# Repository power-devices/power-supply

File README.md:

# Welcome to the Power Supply electronics repository

I teach power electronics and I want to provide my students the best experience possible. This is the reason I created this project. I intend to allow people to produce power electronics devices at an extreme low cost. This board required only 2 layers, but this is no problem today due to [JLCPCB](https://jlcpcb.com/) or other manufacturers.

So far, the project is divided into 3 pieces:

 1. Power supply: used to delivery power the other boards, it is compatible with mono-three phase up to 220 VAC
 2. Power bullet: a three phase h-bridge, simple as that
 3. Power brain F103: the main controller

# Disclaimer

I provide no warranty at all. Use it at your own risk!

# What will I find here?

You will find the design and production files. To edit the schematic/board you will need to install Kicad. I used version 7 to create this board.

# What can I do with this?

In this repository the board design and production files are stored. You are welcome to download/distribute it, use it, whatever.

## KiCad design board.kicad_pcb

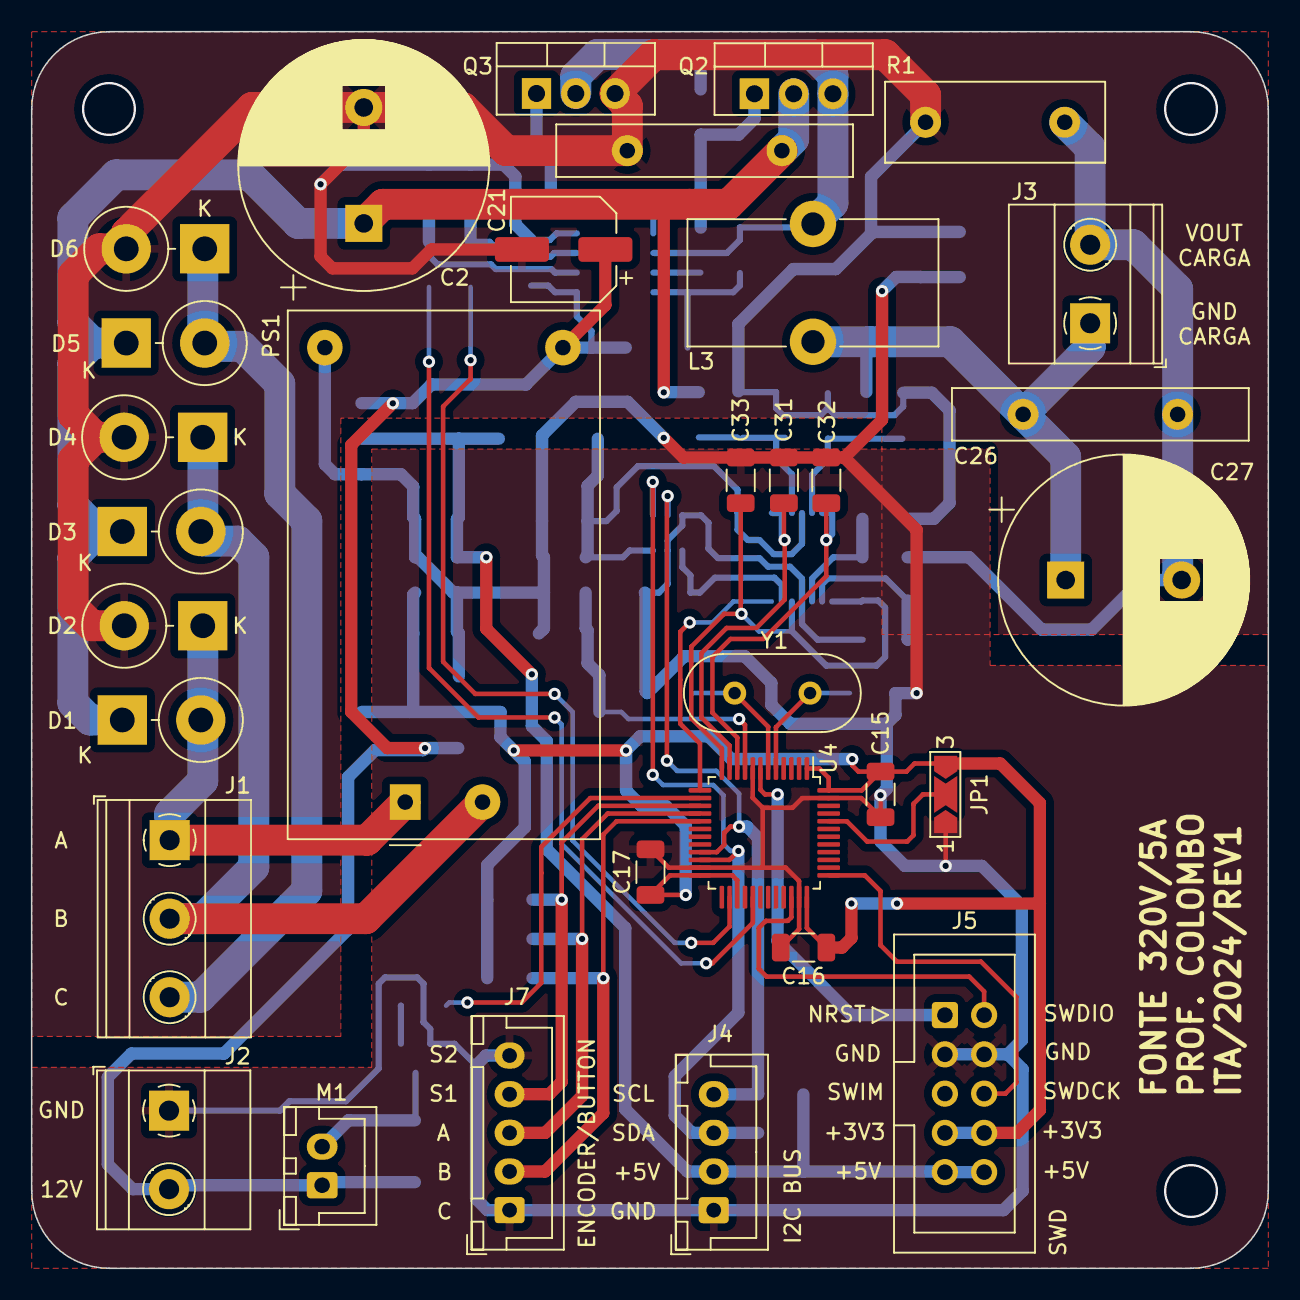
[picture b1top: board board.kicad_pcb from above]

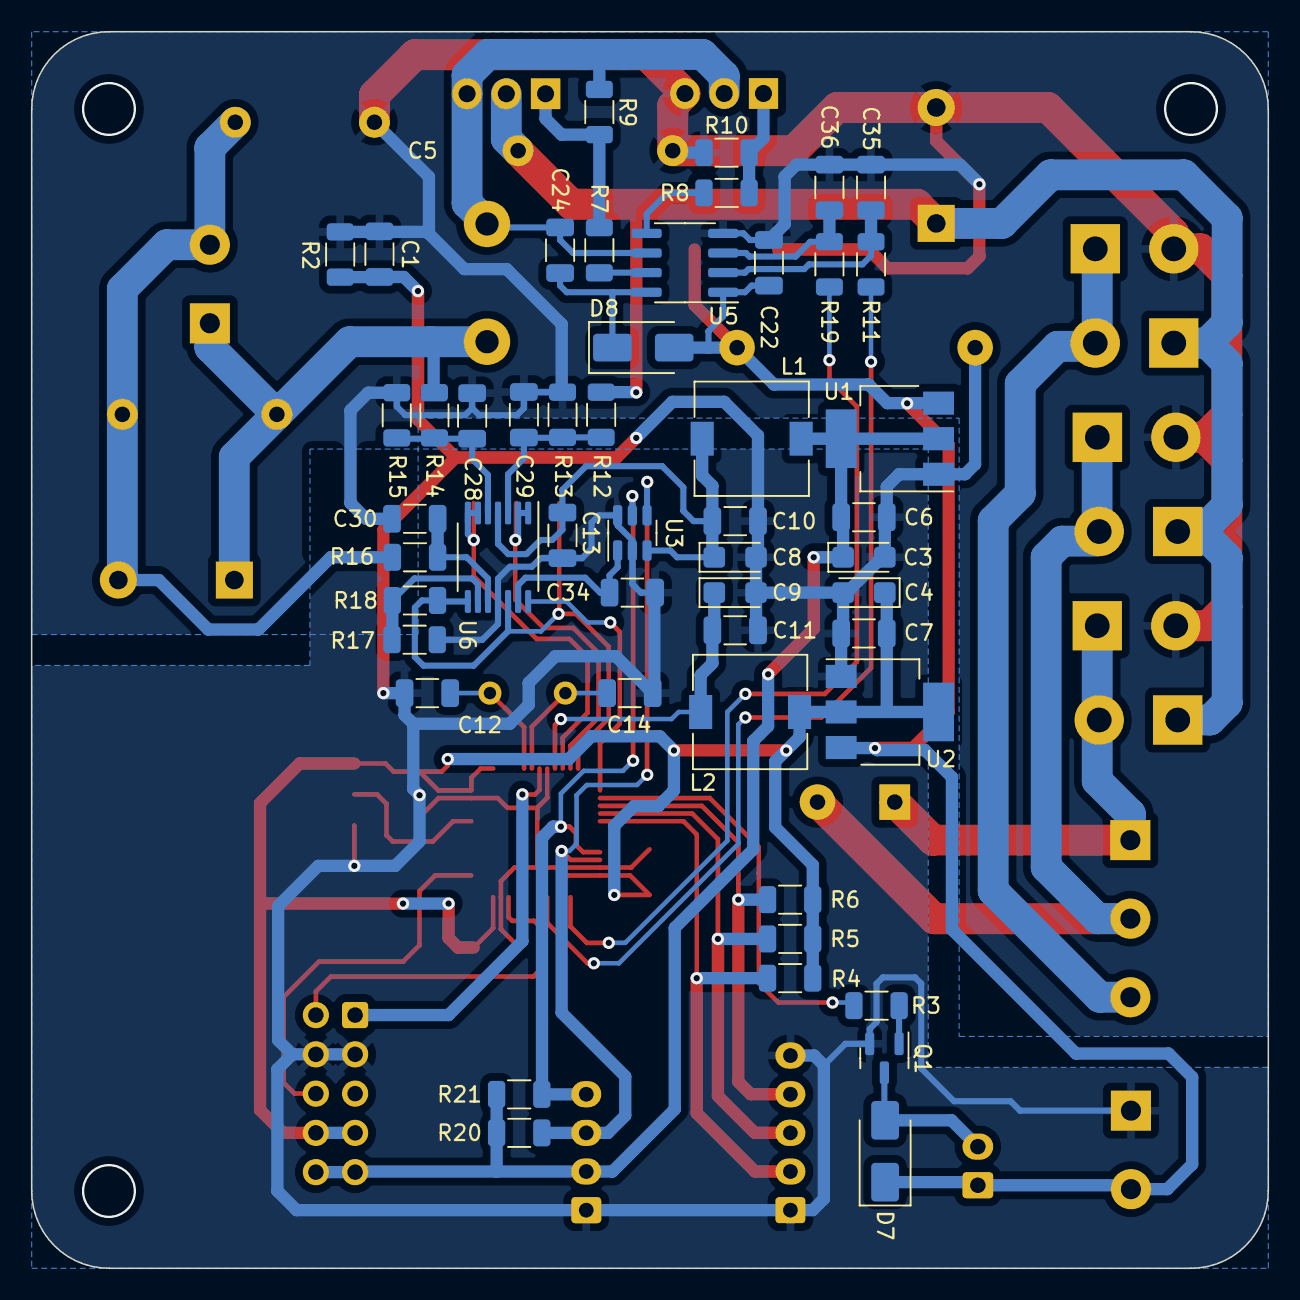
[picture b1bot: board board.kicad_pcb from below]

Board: 2 copper layers, 80.0 x 80.0 mm, 82 parts (50 on the bottom side), 46 nets.

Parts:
C1, C6, C7, C10, C11, C15, C22, C24: 1uF; C_1206_3216Metric
C2, C27: 47uF; CP_Radial_D16.0mm_P7.50mm
C3, C4, C8, C9: 10uF; CP_EIA-3216-18_Kemet-A
C5, C26: 100nF; C_Disc_D19.0mm_W3.0mm_P10.00mm
C12, C14: 22pF; C_1206_3216Metric
C13, C16, C17: 100nF; C_1206_3216Metric
C21: 100uF; CP_Elec_6.3x7.7
C28, C29: 2n2; C_1206_3216Metric
C30: 3n3; C_1206_3216Metric
C31, C32, C33, C34: 10nF; C_1206_3216Metric
C35, C36: 33nF; C_1206_3216Metric
D1, D2, D3, D4, D5, D6: 1N5408; D_DO-201AD_P5.08mm_Vertical_KathodeUp
D7: SS14; D_SMA
D8: 1N4007; D_SMA
J1: Screw_Terminal_01x03; TerminalBlock_Phoenix_MKDS-1,5-3-5.08_1x03_P5.08mm_Horizont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
J2, J3: Screw_Terminal_01x02; TerminalBlock_Phoenix_MKDS-1,5-2-5.08_1x02_P5.08mm_Horizont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
J4: I2C; JST_XH_B4B-XH-A_1x04_P2.50mm_Vertical
J5: SWD; IDC-Header_2x05_P2.54mm_Vertical
J7: ENCODER; JST_XH_B5B-XH-A_1x05_P2.50mm_Vertical
JP1: SolderJumper-3_P2.0mm_Open_TrianglePad1.0x1.5mm_NumberLabels
L1, L2: 100uH; L_7.3x7.3_H4.5
L3: 1mH; L_Toroid_Vertical_L16.0mm_W8.0mm_P7.62mm
M1: Fan; JST_XH_B2B-XH-A_1x02_P2.50mm_Vertical
PS1: HLK-PM12; Converter_ACDC_HiLink_HLK-PMxx
Q1: MMBT3904; SOT-23
Q2, Q3: FDP11N50; TO-220-3_Vertical
R1: 0R1; R_Box_L14.0mm_W5.0mm_P9.00mm
R2: 1R; R_1206_3216Metric
R3, R16: 1k; R_1206_3216Metric
R4, R5, R6, R20, R21: 3k3; R_1206_3216Metric
R7, R8: 47R; R_1206_3216Metric
R9, R10: 10k; R_1206_3216Metric
R11, R19: 100R; R_1206_3216Metric
R12, R14: 180k; R_1206_3216Metric
R13, R15: 1k5; R_1206_3216Metric
R17: 6k8; R_1206_3216Metric
R18: 33k; R_1206_3216Metric
U1: AMS1117-5.0; SOT-223-3_TabPin2
U2: AMS1117-3.3; SOT-223-3_TabPin2
U3: MCP4725xxx-xCH; SOT-23-6
U4: STM32F103C8Tx; LQFP-48_7x7mm_P0.5mm
U5: IR2101; SOIC-8_3.9x4.9mm_P1.27mm
U6: LM324; TSSOP-14_4.4x5mm_P0.65mm
Y1: 16MHz; Crystal_HC49-4H_Vertical

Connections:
+3.3V: C4.1, C7.1, C15.1, C16.1, C17.1, J5.7, J5.8, JP1.3 (B), L2.1, R4.1, R5.1, R6.1, U2.2 (VO), U4.1 (VBAT), U4.24 (VDD), U4.27 (PB14), U4.36 (VDD), U4.48 (VDD)
+3.3VA: C9.1, C11.1, L2.2, U4.9 (VDDA)
+5V: C3.1, C6.1, J4.2, J5.9, J5.10, L1.1, R20.1, R21.1, U1.2 (VO)
+5VA: C8.1, C10.1, C13.1, L1.2, U3.3 (VDD), U6.4 (V+)
+12V: C21.1, C22.1, D7.1 (K), D8.2 (A), J2.2, M1.1 (+), PS1.4 (+Vout), U1.3 (VI), U2.3 (VI), U5.1 (VCC)
/AC-CC converter/PHASE_A: D1.2 (A), D2.1 (K), J1.1, PS1.1 (AC/L)
/AC-CC converter/PHASE_B: D3.2 (A), D4.1 (K), J1.2, PS1.2 (AC/N)
/AC-CC converter/PHASE_C: D5.2 (A), D6.1 (K), J1.3
/Driver/GND_OUT: C26.2, C27.2, J3.2, R1.1, R16.1
/Driver/HIN: R11.1, U4.29 (PA8)
/Driver/LIN: R19.1, U4.26 (PB13)
/Driver/VOUT: C26.1, C27.1, J3.1, L3.1, R14.1
/MCU/BOOT0: JP1.2 (C), U4.44 (BOOT0)
/MCU/BUTTON: J7.4, R6.2, U4.15 (PA5)
/MCU/ENCODER_A: J7.3, R5.2, U4.16 (PA6)
/MCU/ENCODER_B: J7.2, R4.2, U4.17 (PA7)
/MCU/FAN: R3.1, U4.14 (PA4)
/MCU/IMAX: C34.1, U3.1 (VOUT), U6.13 (-)
/MCU/NRST: J5.1, U4.7 (NRST)
/MCU/OC: U4.13 (PA3), U6.14
/MCU/SCL: J4.4, R21.2, U3.5 (SCL), U4.21 (PB10)
/MCU/SDA: J4.3, R20.2, U3.4 (SDA), U4.22 (PB11)
/MCU/SENSE_IOUT: C33.1, R18.2, U4.12 (PA2), U6.8, U6.12 (+)
/MCU/SENSE_VIN: C31.1, U4.11 (PA1), U6.1, U6.2 (-)
/MCU/SENSE_VOUT: C32.1, U4.10 (PA0), U6.6 (-), U6.7
/MCU/SWDCK: J5.6, U4.37 (PA14)
/MCU/SWDIO: J5.2, U4.34 (PA13)
/MCU/XTAL1: C12.1, U4.5 (PD0), Y1.1
/MCU/XTAL2: C14.1, U4.6 (PD1), Y1.2
GNDA: C1.1, C3.2, C4.2, C6.2, C7.2, C8.2, C9.2, C10.2, C11.2, C12.2, C13.2, C14.2, C15.2, C16.2, C17.2, C31.2, C32.2, C33.2, C34.2, J2.1, J4.1, J5.3, J5.4, J7.1, J7.5, JP1.1 (A), PS1.3 (-Vout), Q1.2 (E), R2.1, R17.1, U1.1 (GND), U2.1 (GND), U3.2 (VSS), U3.6 (A0), U4.8 (VSSA), U4.23 (VSS), U4.35 (VSS), U4.47 (VSS), U6.11 (V-)
GNDD: C1.2, C2.2, C5.2, C21.2, C22.2, C28.2, C29.2, C30.2, C35.2, C36.2, D2.2 (A), D4.2 (A), D6.2 (A), Q3.3 (S), R1.2, R2.2, R10.2, R13.2, R15.2, U5.4 (COM)
unnamed: D7.2 (A), M1.2 (-), Q1.3 (C)
unnamed: C24.1, D8.1 (K), U5.8 (VB)
unnamed: Q1.1 (B), R3.2
unnamed: Q2.1 (G), R7.2, R9.1
unnamed: C24.2, L3.2, Q2.3 (S), Q3.2 (D), R9.2, U5.6 (VS)
unnamed: Q3.1 (G), R8.2, R10.1
unnamed: C35.1, R11.2, U5.2 (HIN)
unnamed: R7.1, U5.7 (HO)
unnamed: C36.1, R19.2, U5.3 (LIN)
unnamed: R8.1, U5.5 (LO)
unnamed: C29.1, R12.2, R13.1, U6.3 (+)
unnamed: C28.1, R14.2, R15.1, U6.5 (+)
unnamed: C30.1, R16.2, U6.10 (+)
unnamed: R17.2, R18.1, U6.9 (-)
VBUS: C2.1, C5.1, D1.1 (K), D3.1 (K), D5.1 (K), Q2.2 (D), R12.1

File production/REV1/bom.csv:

Designator,Footprint,Quantity,Value,LCSC Part #
"C1, C10, C11, C15, C22, C24, C6, C7",1206,8,1uF,
"C12, C14",1206,2,22pF,
"C13, C16, C17",1206,3,100nF,
"C2, C27",CP_Radial_D16.0mm_P7.50mm,2,47uF,
C21,CP_Elec_6.3x7.7,1,100uF,
"C26, C5",C_Disc_D19.0mm_W3.0mm_P10.00mm,2,100nF,
"C28, C29",1206,2,2n2,
"C3, C4, C8, C9",CP_EIA-3216-18_Kemet-A,4,10uF,
C30,1206,1,3n3,
"C31, C32, C33, C34",1206,4,10nF,
"C35, C36",1206,2,33nF,
"D1, D2, D3, D4, D5, D6",D_DO-201AD_P5.08mm_Vertical_KathodeUp,6,1N5408,
D7,D_SMA,1,SS14,
D8,D_SMA,1,1N4007,
J1,"TerminalBlock_Phoenix_MKDS-1,5-3-5.08_1x03_P5.08mm_Horizontal",1,Screw_Terminal_01x03,
"J2, J3","TerminalBlock_Phoenix_MKDS-1,5-2-5.08_1x02_P5.08mm_Horizontal",2,Screw_Terminal_01x02,
J4,JST_XH_B4B-XH-A_1x04_P2.50mm_Vertical,1,I2C,
J5,IDC-Header_2x05_P2.54mm_Vertical,1,SWD,
J7,JST_XH_B5B-XH-A_1x05_P2.50mm_Vertical,1,ENCODER,
JP1,SolderJumper-3_P2.0mm_Open_TrianglePad1.0x1.5mm_NumberLabels,1,~,
"L1, L2",L_7.3x7.3_H4.5,2,100uH,
L3,L_Toroid_Vertical_L16.0mm_W8.0mm_P7.62mm,1,1mH,
M1,JST_XH_B2B-XH-A_1x02_P2.50mm_Vertical,1,Fan,
PS1,Converter_ACDC_HiLink_HLK-PMxx,1,HLK-PM12,
Q1,SOT-23,1,MMBT3904,
"Q2, Q3",TO-220-3_Vertical,2,FDP11N50,
R1,R_Box_L14.0mm_W5.0mm_P9.00mm,1,0R1,
"R10, R9",1206,2,10k,
"R11, R19",1206,2,100R,
"R12, R14",1206,2,180k,
"R13, R15",1206,2,1k5,
"R16, R3",1206,2,1k,
R17,1206,1,6k8,
R18,1206,1,33k,
R2,1206,1,1R,
"R20, R21, R4, R5, R6",1206,5,3k3,
"R7, R8",1206,2,47R,
U1,SOT-223-3_TabPin2,1,AMS1117-5.0,
U2,SOT-223-3_TabPin2,1,AMS1117-3.3,
U3,SOT-23-6,1,MCP4725xxx-xCH,
U4,LQFP-48_7x7mm_P0.5mm,1,STM32F103C8Tx,
U5,SOIC-8_3.9x4.9mm_P1.27mm,1,IR2101,
U6,TSSOP-14_4.4x5mm_P0.65mm,1,LM324,
Y1,Crystal_HC49-4H_Vertical,1,16MHz,

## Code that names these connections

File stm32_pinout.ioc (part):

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Mcu.Name=STM32F103C(8-B)Tx
Mcu.Package=LQFP48
Mcu.UserName=STM32F103C8Tx
PA0-WKUP.Signal=ADCx_IN0
PA1.Signal=ADCx_IN1
PA13.Mode=Serial_Wire
PA13.Signal=SYS_JTMS-SWDIO
PA14.Mode=Serial_Wire
PA14.Signal=SYS_JTCK-SWCLK
PA2.Signal=ADCx_IN2
PA6.Signal=S_TIM3_CH1
PA7.Signal=S_TIM3_CH2
PB10.Mode=I2C
PB10.Signal=I2C2_SCL
PB11.Mode=I2C
PB11.Signal=I2C2_SDA
PD0-OSC_IN.Mode=HSE-External-Oscillator
PD0-OSC_IN.Signal=RCC_OSC_IN
PD1-OSC_OUT.Mode=HSE-External-Oscillator
PD1-OSC_OUT.Signal=RCC_OSC_OUT
board=custom

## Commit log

2023-11-22 Added the REV1 files.
2023-11-22 Added a README file.
2023-11-22 Fixed wrong links.
2023-11-22 Cropped images.
